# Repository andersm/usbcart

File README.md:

usbcart
=======
A USB development cartridge with accompanying tools for the Sega Saturn. [See here for more info](http://www.iki.fi/anders.montonen/sega/usbcart.html).

usbcart-kicad
-------------
Kicad design files for the cartridge.

usbcart-mfg
-----------
Manufacturing files for the cartridge.

arflasher
---------
Tool for flashing Sega Saturn cartridges.

cartrom
-------
A ROM image for the USB cartridge.

ftx
---
A file-transfer tool for the USB cartridge for Unix-like systems. Depends on [libftdi](http://www.intra2net.com/en/developer/libftdi/ "libftdi").

The hardware design is released under the terms of the [Creative Commons Attribution-ShareAlike 3.0 Unported (CC BY-SA 3.0)](http://creativecommons.org/licenses/by-sa/3.0/) license.

License for the packages in the "walter" subdirectory:

    Kicad 3d Packages by W. Lain - kcswalter@member.fsf.org

    These packages are released under the terms of the Creative Commons license v3.0, Attribution-Share Alike.

    The author holds no responsibility for any damage that can be caused by the usage of these 3d models. You are however welcome to report any error or discrepance to the author, provided that you give also the correct information and its source (i.e. the correct datasheet).
    Note that the author used publicly available data sheets from many different companies, and that package dimensions may vary slightly between companies.

The software components are released under a BSD 2-Clause license. See the individual source files for details.

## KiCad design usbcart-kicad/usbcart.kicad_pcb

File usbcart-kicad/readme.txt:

USB Flash Cartridge for the Sega Saturn by Anders Montonen
<http://www.iki.fi/Anders.Montonen/sega/usbcart/>

Released under the terms of the Creative Commons Attribution-ShareAlike 3.0 Unported (CC BY-SA 3.0) license.
<http://creativecommons.org/licenses/by-sa/3.0/>

License for the packages in the "walter" subdirectory:
======================================================

Kicad 3d Packages by W. Lain - kcswalter@member.fsf.org

These packages are released under the terms of the Creative Commons license v3.0, Attribution-Share Alike.

The author holds no responsibility for any damage that can be caused by the usage of these 3d models. You are however welcome to report any error or discrepance to the author, provided that you give also the correct information and its source (i.e. the correct datasheet).
Note that the author used publicly available data sheets from many different companies, and that package dimensions may vary slightly between companies.

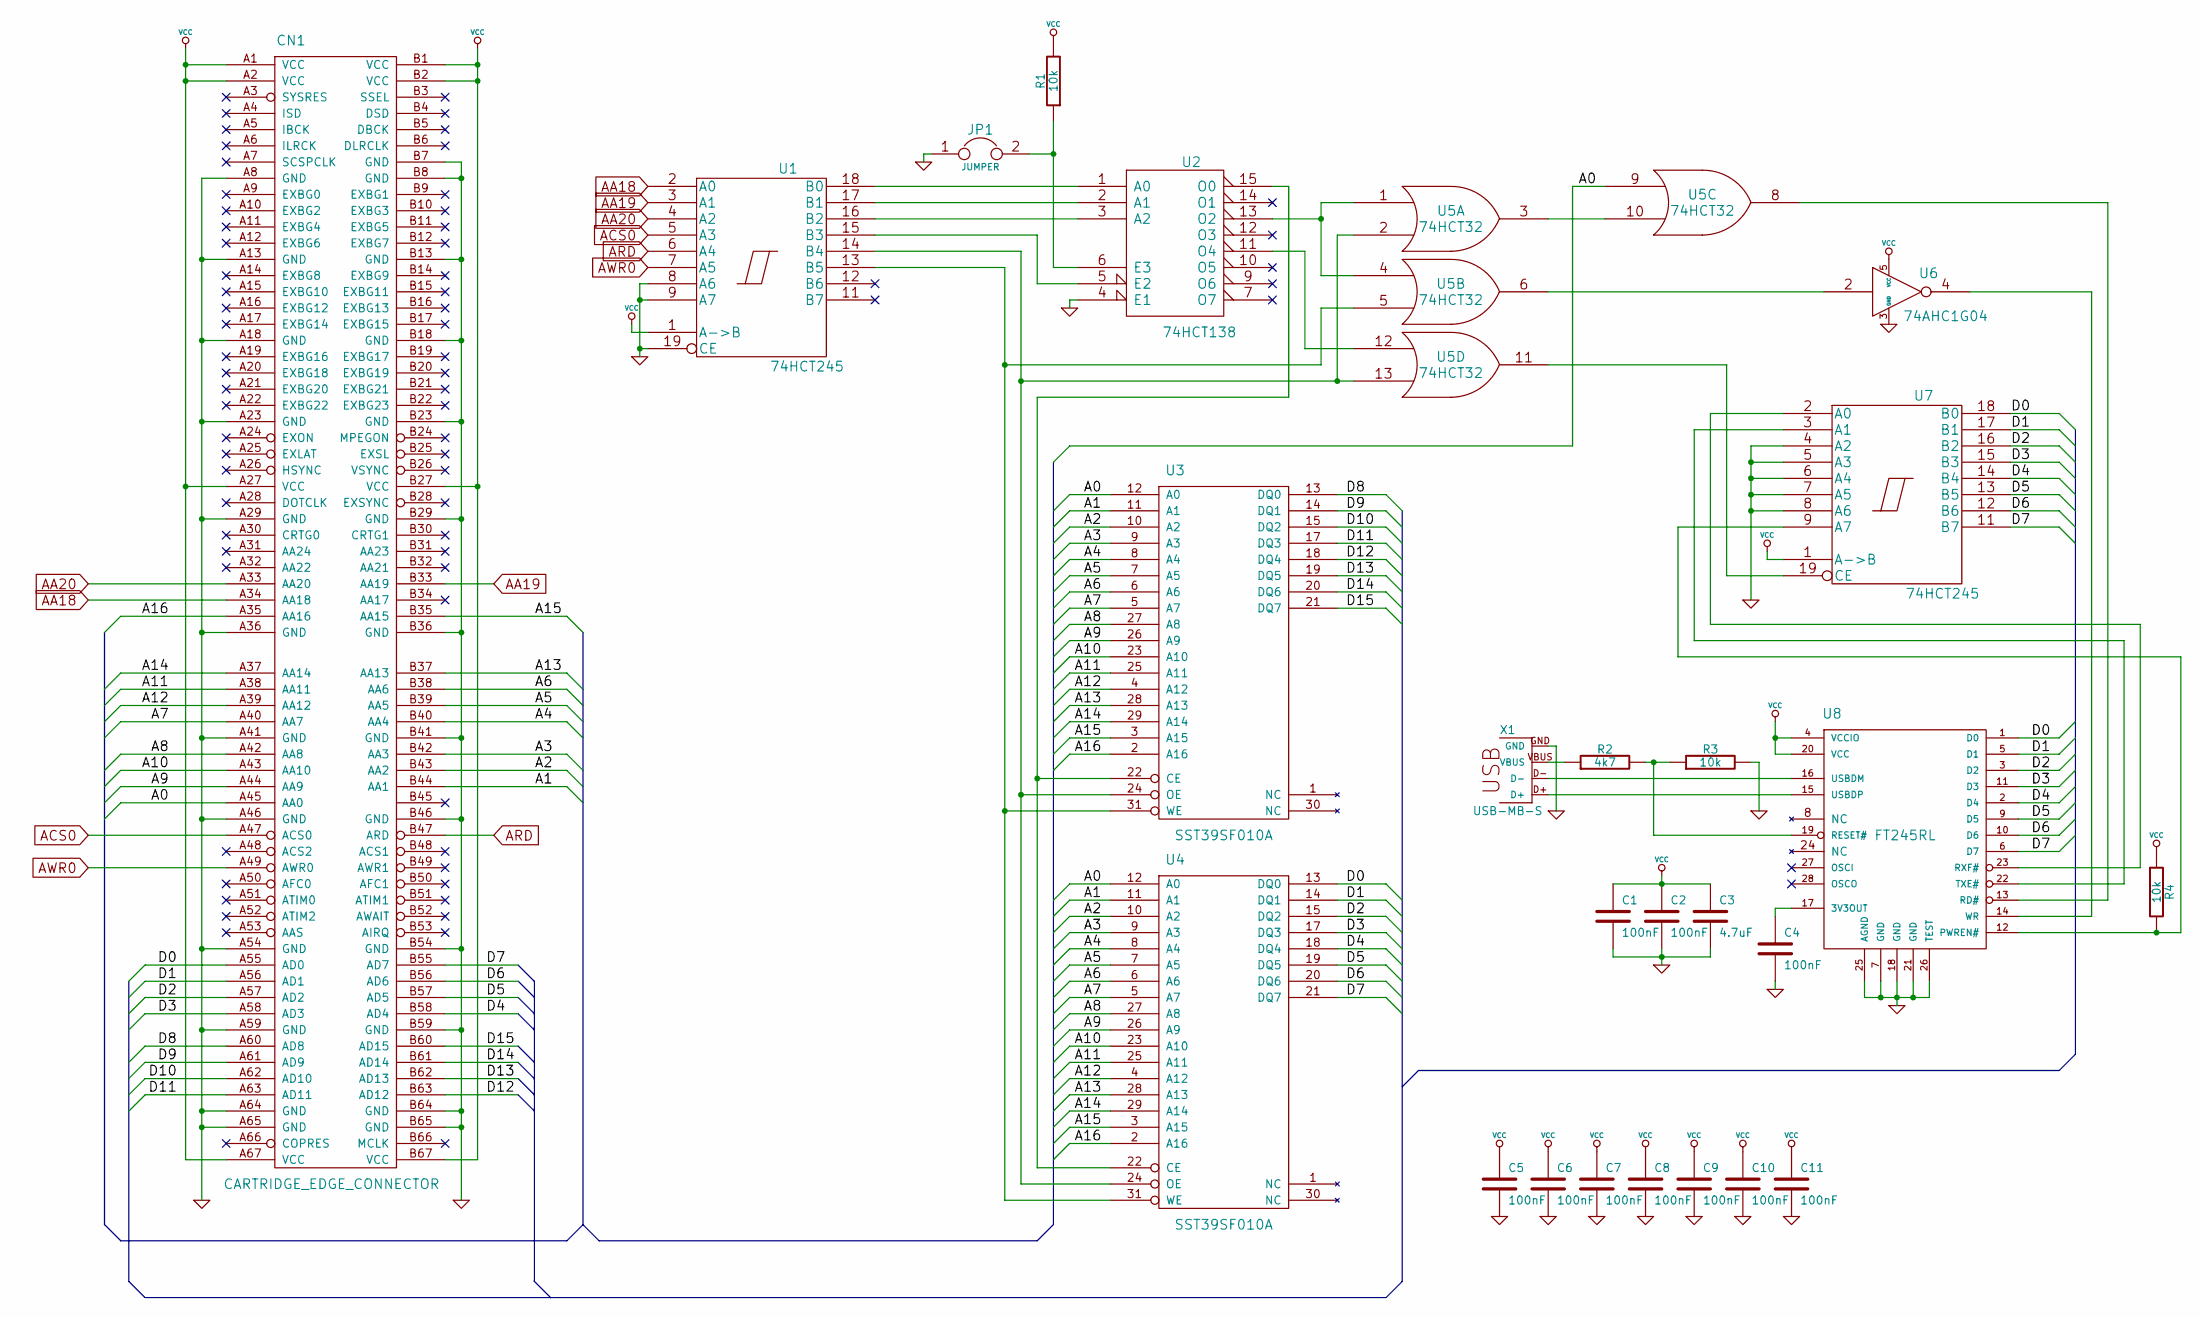
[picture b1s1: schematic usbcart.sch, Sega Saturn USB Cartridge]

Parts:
C1, C2, C4: 100nF; SM0603
C3: 4.7uF; SM0603
C5, C6, C7, C8, C9, C10, C11: 100nF
CN1: CARTRIDGE_EDGE_CONNECTOR; CARTRIDGE_EDGE_CONNECTOR2
JP1: JUMPER; SIL-2
R1, R3, R4: 10k; SM0603
R2: 4k7; SM0603
U1, U7: 74HCT245; soic-20
U2: 74HCT138; so-16
U3, U4: SST39SF010A; PLCC32
U5: 74HCT32; so-14
U6: 74AHC1G04; SOT23-5
U8: FT245RL; SSOP28
X1: USB-MB-S; con-usb-USB-MB-S

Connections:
/A0: CN1.A45 (AA0), U3.12 (A0), U4.12 (A0), U5.9
/A1: CN1.B44 (AA1), U3.11 (A1), U4.11 (A1)
/A2: CN1.B43 (AA2), U3.10 (A2), U4.10 (A2)
/A3: CN1.B42 (AA3), U3.9 (A3), U4.9 (A3)
/A4: CN1.B40 (AA4), U3.8 (A4), U4.8 (A4)
/A5: CN1.B39 (AA5), U3.7 (A5), U4.7 (A5)
/A6: CN1.B38 (AA6), U3.6 (A6), U4.6 (A6)
/A7: CN1.A40 (AA7), U3.5 (A7), U4.5 (A7)
/A8: CN1.A42 (AA8), U3.27 (A8), U4.27 (A8)
/A9: CN1.A44 (AA9), U3.26 (A9), U4.26 (A9)
/A10: CN1.A43 (AA10), U3.23 (A10), U4.23 (A10)
/A11: CN1.A38 (AA11), U3.25 (A11), U4.25 (A11)
/A12: CN1.A39 (AA12), U3.4 (A12), U4.4 (A12)
/A13: CN1.B37 (AA13), U3.28 (A13), U4.28 (A13)
/A14: CN1.A37 (AA14), U3.29 (A14), U4.29 (A14)
/A15: CN1.B35 (AA15), U3.3 (A15), U4.3 (A15)
/A16: CN1.A35 (AA16), U3.2 (A16), U4.2 (A16)
/D0: CN1.A55 (AD0), U4.13 (DQ0), U7.18 (B0), U8.1 (D0)
/D1: CN1.A56 (AD1), U4.14 (DQ1), U7.17 (B1), U8.5 (D1)
/D2: CN1.A57 (AD2), U4.15 (DQ2), U7.16 (B2), U8.3 (D2)
/D3: CN1.A58 (AD3), U4.17 (DQ3), U7.15 (B3), U8.11 (D3)
/D4: CN1.B58 (AD4), U4.18 (DQ4), U7.14 (B4), U8.2 (D4)
/D5: CN1.B57 (AD5), U4.19 (DQ5), U7.13 (B5), U8.9 (D5)
/D6: CN1.B56 (AD6), U4.20 (DQ6), U7.12 (B6), U8.10 (D6)
/D7: CN1.B55 (AD7), U4.21 (DQ7), U7.11 (B7), U8.6 (D7)
/D8: CN1.A60 (AD8), U3.13 (DQ0)
/D9: CN1.A61 (AD9), U3.14 (DQ1)
/D10: CN1.A62 (AD10), U3.15 (DQ2)
/D11: CN1.A63 (AD11), U3.17 (DQ3)
/D12: CN1.B63 (AD12), U3.18 (DQ4)
/D13: CN1.B62 (AD13), U3.19 (DQ5)
/D14: CN1.B61 (AD14), U3.20 (DQ6)
/D15: CN1.B60 (AD15), U3.21 (DQ7)
AA18: CN1.A34 (AA18), U1.2 (A0)
AA19: CN1.B33 (AA19), U1.3 (A1)
AA20: CN1.A33 (AA20), U1.4 (A2)
ACS0: CN1.A47 (ACS0), U1.5 (A3)
ARD: CN1.B47 (ARD), U1.6 (A4)
AWR0: CN1.A49 (AWR0), U1.7 (A5)
GND: C1.2, C2.2, C3.2, C4.2, C5.2, C6.2, C7.2, C8.2, C9.2, C10.2, C11.2, CN1.A8 (GND), CN1.A13 (GND), CN1.A18 (GND), CN1.A23 (GND), CN1.A29 (GND), CN1.A36 (GND), CN1.A41 (GND), CN1.A46 (GND), CN1.A54 (GND), CN1.A59 (GND), CN1.A64 (GND), CN1.A65 (GND), CN1.B7 (GND), CN1.B8 (GND), CN1.B13 (GND), CN1.B18 (GND), CN1.B23 (GND), CN1.B29 (GND), CN1.B36 (GND), CN1.B41 (GND), CN1.B46 (GND), CN1.B54 (GND), CN1.B59 (GND), CN1.B64 (GND), CN1.B65 (GND), JP1.1, R3.2, U1.8 (A6), U1.9 (A7), U1.10 (GND), U1.19 (CE), U2.4 (E1), U2.8 (GND), U3.16 (GND), U4.16 (GND), U5.7 (GND), U6.3 (GND), U7.4 (A2), U7.5 (A3), U7.6 (A4), U7.7 (A5), U7.8 (A6), U7.10 (GND), U8.7 (GND), U8.18 (GND), U8.21 (GND), U8.25 (AGND), U8.26 (TEST), X1.GND
unnamed: U5.8, U8.13 (RD#)
unnamed: U7.2 (A0), U8.23 (RXF#)
unnamed: U8.16 (USBDM), X1.D-
unnamed: C4.1, U8.17 (3V3OUT)
unnamed: R2.2, R3.1, U8.19 (RESET#)
unnamed: R4.2, U7.9 (A7), U8.12 (PWREN#)
unnamed: U6.4, U8.14 (WR)
unnamed: U5.11, U7.19 (CE)
unnamed: U5.6, U6.2
unnamed: U5.3, U5.10
unnamed: U2.11 (O4), U5.12
unnamed: U2.13 (O2), U5.1, U5.4
unnamed: JP1.2, R1.1, U2.6 (E3)
unnamed: U7.3 (A1), U8.22 (TXE#)
unnamed: U1.14 (B4), U3.24 (OE), U4.24 (OE), U5.2, U5.13
unnamed: U1.16 (B2), U2.3 (A2)
unnamed: U1.17 (B1), U2.2 (A1)
unnamed: U1.18 (B0), U2.1 (A0)
unnamed: U1.13 (B5), U3.31 (WE), U4.31 (WE), U5.5
unnamed: U2.15 (O0), U3.22 (CE), U4.22 (CE)
unnamed: U8.15 (USBDP), X1.D+
unnamed: R2.1, X1.VBUS
unnamed: U1.15 (B3), U2.5 (E2)
VCC: C1.1, C2.1, C3.1, C5.1, C6.1, C7.1, C8.1, C9.1, C10.1, C11.1, CN1.A1 (VCC), CN1.A2 (VCC), CN1.A27 (VCC), CN1.A67 (VCC), CN1.B1 (VCC), CN1.B2 (VCC), CN1.B27 (VCC), CN1.B67 (VCC), R1.2, R4.1, U1.1 (A->B), U1.20 (VCC), U2.16 (VCC), U3.32 (VCC), U4.32 (VCC), U5.14 (VCC), U6.5 (VCC), U7.1 (A->B), U7.20 (VCC), U8.4 (VCCIO), U8.20 (VCC)

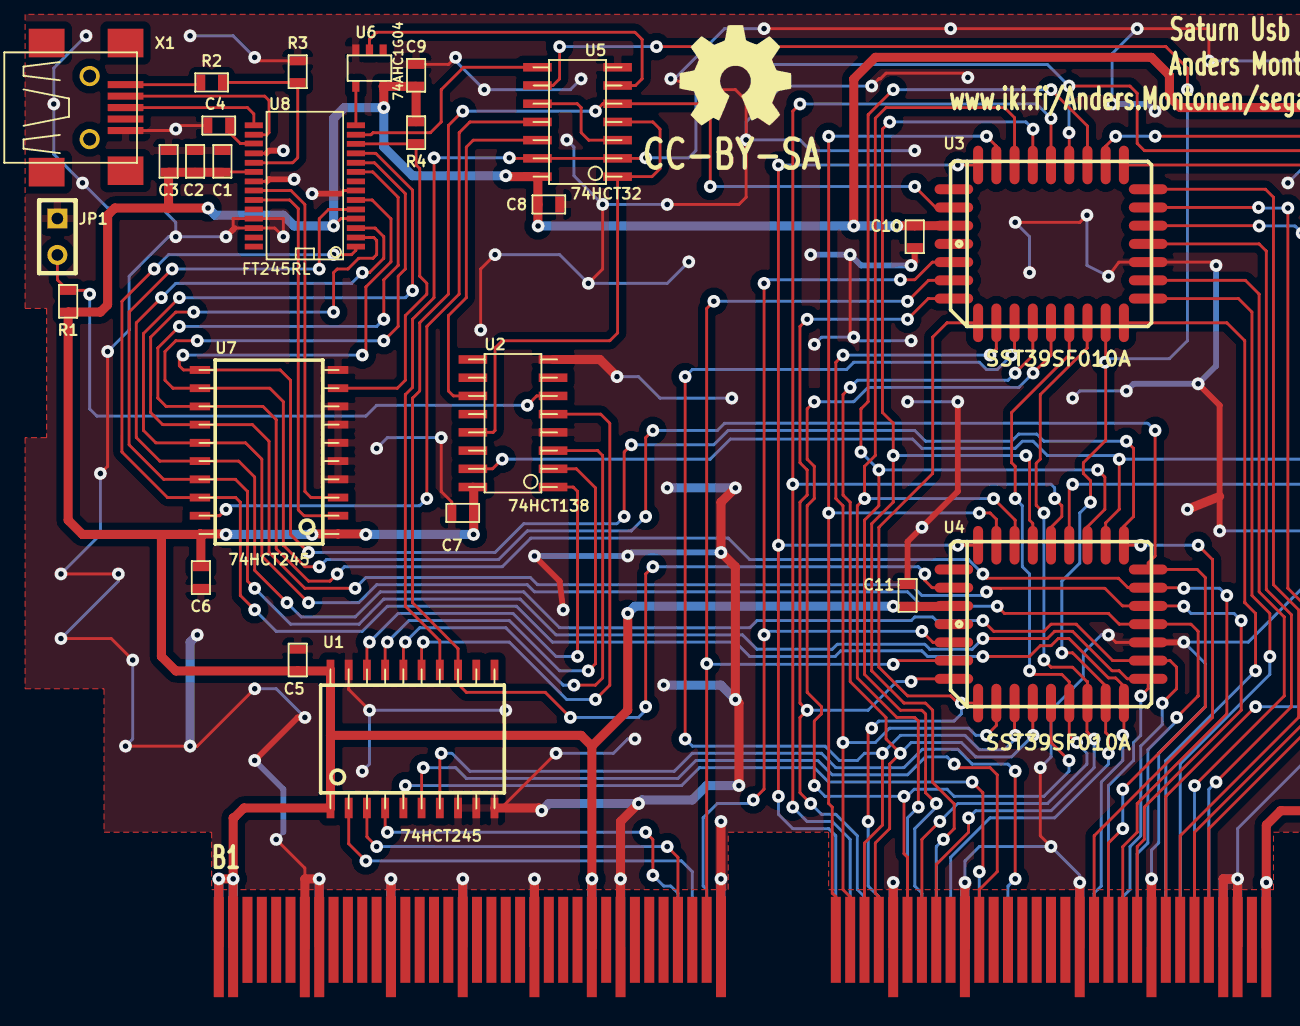
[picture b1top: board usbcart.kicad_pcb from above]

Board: 2 copper layers, 26 parts (0 on the bottom side), 64 nets.

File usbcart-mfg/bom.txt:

C1         100nF       0603
C2         100nF       0603
C3         4.7uF       0603
C4         100nF       0603
C5         100nF       0603
C6         100nF       0603
C7         100nF       0603
C8         100nF       0603
C9         100nF       0603
C10        100nF       0603
C11        100nF       0603
JP1        JUMPER      0.1" header (optional)
R1         10k         0603
R2         4k7         0603
R3         10k         0603
R4         10k         0603
U1         74HCT245    SOIC-20 (eg. Texas Instruments SN74HCT245DW)
U2         74HCT138    SOIC-16 (eg. Fairchild MC74HCT138ADG)
U3         SST39SF010A PLCC32
U4         SST39SF010A PLCC32
U5         74HCT32     SO-14 (eg. NXP 74HCT32D,653)
U6         74AHC1G04   SOT23-5 (eg. Texas Instruments SN74AHC1G04QDBVRQ1)
U7         74HCT245    SOIC-20 (eg. Texas Instruments SN74HCT245DW)
U8         FT245RL     SSOP28
X1         USB-MB-S    Surface mount mini USB B connector (eg. Wurth 65100516121)

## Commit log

2013-02-14 Import files.
2013-02-24 Fixed an omitted license change
2015-04-16 Added schematic library file
2015-04-17 Libraries and board converted to new kicad format. Card edge connector modified for hotplug support.
2015-05-13 Small Makefile improvements.
2015-05-14 Tweak Makefile.
2015-05-14 Refactor to reduce code duplication.
2015-05-14 Status bytes are only included in IN transfers.
2015-05-14 Add command for running code from specified address.
2015-05-17 Fix compiler warning.
2015-05-17 Add build configuration for easier testing.
2015-05-20 Use DMA when transferring data from the host to the Saturn.
2015-05-20 Minor cleanups.
2015-05-20 Bump version number.
2015-05-21 Small cleanup.
2015-05-24 Revert earlier change. This form is more readable.
2015-05-24 Changing the A-bus settings does not actually seem to matter.
2015-05-24 Update copyright headers.
2016-07-01 Remove duplicate register definition
2016-07-01 Rearrange DMAC registers in address order
2016-07-01 Minor cleanup
2016-07-01 Refactor DMA transfer code
    Simplify the inner loop, allowing all the code to be inlined.
2019-07-03 Add explanation of the DMA transfer logic
2020-04-09 Fix schematic importing into KiCad 5.1
2020-04-09 Remove executable bits from files
2020-04-13 Add missing KiCad cache library
2020-04-13 Don't ignore KiCad cache libraries
2020-04-14 Fix link to info page

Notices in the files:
usbcart-kicad/usbcart.kicad_pcb:
Distributed under the CC-BY-SA license
